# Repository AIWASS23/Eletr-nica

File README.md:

# Protheus

Projetos das cadeias de eletrônicas

## 📋 Pré-requisitos

Software Proteus <br>
Software MPLAB <br>

## 🛠️ Construído com

* [Proteus](https://www.labcenter.com/downloads/) - Software para prototipação de Hardware
* [MPLAB](https://www.microchip.com/en-us/tools-resources/develop/mplab-x-ide) - IDE para desenvolvimento de software

## 🖇️ Colaborando

Veja o arquivo [CONTRIBUTING.md](https://github.com/AIWASS23/Protheus/blob/main/CONTRIBUTING) para detalhes.

## 📌 Versão

| Version | Supported          |
| ------- | ------------------ |
| 1.0     | :white_check_mark: |

## ✒️ Autores

* **Marcelo De Araújo** - *Desenvolvimento de Hardware e Software* - [Marcelo de Araújo](https://github.com/AIWASS23)

## 📄 Licença

Este projeto está sob a licença (GNU) - veja o arquivo [LICENSE.md](https://github.com/AIWASS23/Protheus/blob/main/LICENSE) para detalhes.

## 🎁 Expressões de gratidão

Agradeço ao Professor Bento pela inspiração

---
⌨️ com ❤️ por [Marcelo De Araújo](https://gist.github.com/AIWASS23) 😊

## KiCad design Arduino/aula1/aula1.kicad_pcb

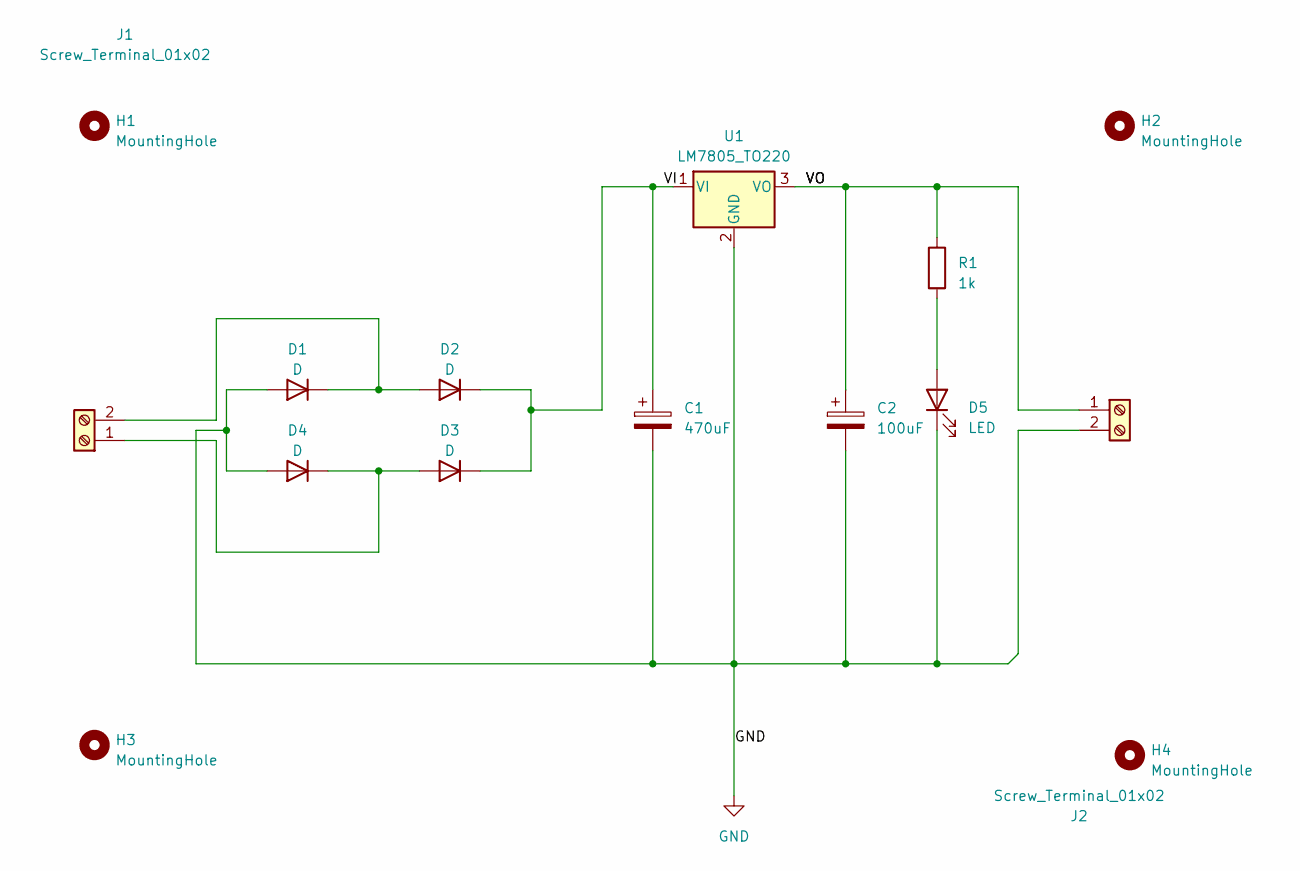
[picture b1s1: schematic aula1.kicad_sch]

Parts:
C1: 470uF; CP_Radial_D4.0mm_P1.50mm
C2: 100uF; CP_Radial_D4.0mm_P1.50mm
D1, D2, D3, D4: D; D_DO-41_SOD81_P10.16mm_Horizontal
D5: LED; LED_D5.0mm
H1, H2, H3, H4: MountingHole; MountingHole_5mm
J1, J2: Screw_Terminal_01x02; TerminalBlock_bornier-2_P5.08mm
R1: 1k; R_Axial_DIN0207_L6.3mm_D2.5mm_P10.16mm_Horizontal
U1: LM7805_TO220; TO-220-3_Vertical

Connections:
/VI: C1.1, D2.1 (K), D3.1 (K), U1.1 (VI)
/VO: C2.1, J2.1, R1.1, U1.3 (VO)
GND: C1.2, C2.2, D1.2 (A), D4.2 (A), D5.1 (K), J2.2, U1.2 (GND)
unnamed: D1.1 (K), D2.2 (A), J1.2
unnamed: D3.2 (A), D4.1 (K), J1.1
unnamed: D5.2 (A), R1.2

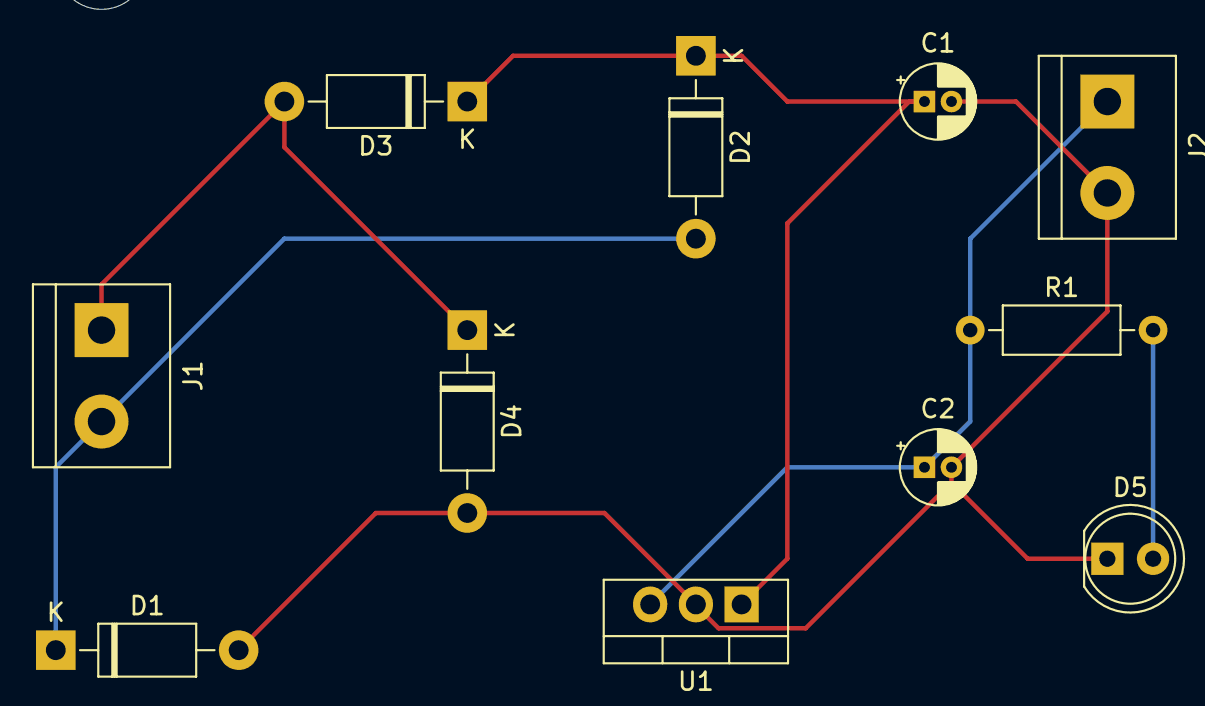
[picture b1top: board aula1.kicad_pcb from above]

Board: 2 copper layers, 15 parts (0 on the bottom side), 6 nets.

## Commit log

2022-11-10 MCMP
2022-11-10 README MCMP
2022-11-11 Atualização de Arquivos
2022-11-12 Atualização de Eletronica Analogica
2022-12-11 Micro Controladores
2022-12-11 Micro Processadores
2022-12-11 Micro Processadores 💻
2022-12-11 Micro Processadores e Controladores
2022-12-16 Lista final de MCMP 🥳
2022-12-16 Update issue templates
    Update issue templates
2022-12-16 Create Security policy
2022-12-16 Create Code Of Conduct
2022-12-16 Create Contributing
2022-12-16 Finalização da disciplina MPMC
2023-06-13 Arduino
2023-06-13 Slides de Estudo
2023-06-21 Sistemas Lineares
